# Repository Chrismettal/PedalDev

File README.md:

# PedalDev <!-- omit in toc -->

This is a convenient system for quickly creating stompboxes, as well as a collection of designs made with this system.

The design is split into two boards, a lower and an upper one. The lower PCB handles all of the I/O, switching, and power stuff, while the upper one focuses on the individual effect. The two boards plug together and fit neatly inside a commonly used Hammond 1590B. For each finished design there is also a PCB frontpanel so I don't have to deal with any actual design work and can just hide my designs behind technical looking stuff. The actual boards take full advantage of modern SMD components for optimal space usage.

All designs build up from the same template to allow rapid creation of new designs as well as saving time on recurring steps. There are even various protoboard variants of the upper PCB fitting the same template, to make boutique one-off designs more convenient and robust. For every design you will find the full KiCAD project including schematic and production files like **BOM, Gerbers and PCBA place files** in their respective project folders. (`/pcb/*`)

For easy mechanical manufacturing a 3D printable drilling template is provided. There is also a 3D printable design of the full stompbox similar to the 1590B with all ports "predrilled". A plastic case is not super recommended though and should only be used for quick testing. Conductive spray paint as shielding on the inside is also recommended when using the 3D printed case. (`/3d/*`)

Parts marked with ":construction:" are work in progress and not fully verified yet.

---

Individual boards, predrilled cases as well as kits will be stocked at Tindie!

**If you like my work please consider [supporting my caffeine addiction](https://github.com/Chrismettal#donations)!**

## Table of contents <!-- omit in toc -->

- [Specific Designs](#specific-designs)
  - [404 (:sheep: Ibanez Tubescreamer)](#404-sheep-ibanez-tubescreamer)
  - [YOU WHAT?! (:sheep: emma electronic PisdiYAUwot)](#you-what-sheep-emma-electronic-pisdiyauwot)
  - [:construction: TOP (:sheep: OKKO Dominator)](#construction-top-sheep-okko-dominator)
- [Common PCBs](#common-pcbs)
  - [Lower](#lower)
  - [:construction: Lower Smart](#construction-lower-smart)
- [Protoboards](#protoboards)
  - [Proto Simple](#proto-simple)
- [Designing your own effects](#designing-your-own-effects)
- [Building guide](#building-guide)
  - [Case](#case)
  - [Electronics](#electronics)
- [Sources](#sources)
- [Tools](#tools)
- [Donations](#donations)
- [License](#license)

## Specific Designs

While there aren't many specific designs right now, they will be created faster now that the system is proven working. There is a wide range of devices in the works, from high gain distortions over reverbs to new, experimental stuff.

### 404 (:sheep: Ibanez Tubescreamer)

Based on the popular Tubescreamer this is obviously the first design to be done in this system.

Nothing crazy here, only `D1-3` feature a dual footprint to put in your favourite clipping diodes.

There are two jumpers that need to be set when building this board. `JP1` does not really do anything with the sound but chooses a filter to be sent to ground or to bias voltage as some schematics have it either way. `JP2` however allows choosing betweeen symmetrical or assymetrical clipping.

### YOU WHAT?! (:sheep: emma electronic PisdiYAUwot)

Very cheap in parts but incredibly tight high gain distortion with lots of attack.

### :construction: TOP (:sheep: OKKO Dominator)

:construction: :construction: :construction: **Work in progress** :construction: :construction: :construction:

Based on schematic by Saruman [found here](https://www.freestompboxes.org/viewtopic.php?t=12031&hilit=c6).

First PCB version `f35813b` was broken is currently being debugged. 4 Pins on `TL074` were swapped, `ICL7660` does not work when `BOOST` mode is set (But **`ICL7660S`** does..), and input stage sounds super starved, more like a bassy fuzz than a distortion. Simulation seems to confirm this so confidence in schematic is low. Currently getting hold of an original Dominator for schematic comparison.

Two jumpers on board revision `f35813b` are for debugging the power stage around the `7660` but will probably be removed or clarified on the fixed revision

## Common PCBs

### Lower

The lower PCB consists of the bypass footswitch with a status LED, input and output jacks as well as power input, filtering and FET based reverse polarity protection.

The Input/Output jacks are called `PJ-602B`. These are not available via LCSC sadly, but can be found all over Aliexpress. 

Additionally an optional TL07X based buffer can be enabled via two jumpers. This was only added because the PCB had enough room for it and it can save room on the pedalboard instead of adding a separate buffer box. The buffer parts do NOT NEED to be populated if you intend never to use them. **Either `JP1_A1` and `JP1_B1` or `JP2_A1` and `JP2_B1` need to be set for signal to be passed through**.

The LED is driven through a simple "anti pop" filter and two optional anti-pop bleeders can be enabled via `JP3` and `JP4` to bleed any input/output caps on the connected upper board if neccessary.

Test hooks and pads are sprinkled on interesting signals for effect development and debugging.

> :bulb: Hint: 
> 
> While this system is intended to be used with one lower PCB and one upper PCB fitting together, it might be convenient to just use the lower PCB even if you do not intend to use an actual effect from this system. Doing so greatly reduces the amount of free form wiring and frees up some space on your actual effect PCB.

### :construction: Lower Smart

:construction: :construction: :construction: **Work in progress** :construction: :construction: :construction:

Same as `Lower`, but instead of a true bypass 3PDT Switch it features a microcontroller to turn your effect on and off either in momentary or latching mode. To show the mode it's currently on, it uses a bicolor LED.

On initial bootup, the device will be in latching mode. Pressing the button will toggle the effect on and off. The :construction: colored LED will be on as long as the effect is on in toggle mode. 
Holding the button down for 9 seconds, both LEDs will start blinking, signaling that a mode change is imminent. Holding the button for one more second, the device will switch into momentary mode.
In momentary mode, the effect will only be on while the button is held. While the effect is on, a :construction: colored LED will be on in momentary mode.
Switching back to toggle mode works the same way, by holding down the button long enough.

## Protoboards

### Proto Simple

This is a simple protoboard to use as an "upper" board, allowing for up to 6 pots, or 5 pots with one DPDT print switch.
It features 9V and GND power rails straight through the design to allow for easy power distribution

While it does not allow for the density of SMD components it can certainly fit a lot of designs.

## Designing your own effects

I would love to merge your designs using this system into this repo!

To design your own effect PCB, create a copy of the `UpperRaw` KiCAD project for the actual effect, and `FrontRaw` for a PCB frontpanel design. `UpperRaw` includes a collection of frequently used parts in the schematic, set up with LCSC part numbers etc. It would be great if you add LCSC part numbers to all parts used in your design as well. After merging I will recreate the production files to the same parameters as the already created designs so don't worry about that.

---

## Building guide

As the system tries to use the little space in the 1590B as efficient as possible, the actual build can be quite tight. There is a set order of steps that should be taken to make the build as quick and easy as possible.

The whole system is designed so the PCBs can be ordered from JLCPCB mostly populated, so only very little hand soldering is involved. If you order the boards finished you will mostly have to solder only the through hole components, but for some rare components that JLCPCB doesn't populate, it might be neccessary to solder some SMD components manually. SMD components go down to `0603` for passives, and `SOIC-*` / `SOT-*` for actives, which is still hand solderable without too much trouble. A hot air solder station is highly recommended though.

<details>
  <summary markdown="span">Building guide, click to expand</summary>

### Case

If you have access to a 3D printer (or to my [Tindie Shop](https://www.tindie.com/stores/binary-6/)), there is a printable drill guide available. Otherwise, there will be a techdraw sheet with all the dimensions. At the [shop](https://www.tindie.com/stores/binary-6/) you will also find predrilled, black cases directly manufactured by Hammond.

All models are compatible with the same drill layout. Holes not required for a specific board will be hidden by the front plate, so the fully stacked 6 controls variant works for every model.

1. Put the case in the drill guide and use a center punch to mark out all the holes to be drilled

2. Pre-drill all marked holes with a `3mm drill bit` (The smallest size used on the device)

3. Drill out all the holes to the sizes marked on the drill guide. Note that the holes are all 0.5mm - 1mm larger than they need to be to make alignment of the frontpanel easier

4. If you want to paint the case, this would be the step to do it. I clean the case with rubbing alcohol, prime and paint, while only focusing on the sides of the case as I will hide the top underneath the frontpanels.

### Electronics

1. Some boards require several components to be mounted manually (Check their individual [documentation](#specific-designs)). These will include through hole parts or not easily available active parts for example. In this case, the OpAmp and input stage transistors, as well as connectors need to be placed manually. Note that the pots and switches are NOT placed at this stage!

---

2. The lower PCB also requires some assembly, namely attaching the LED with its spacer and soldering on the board-to-board connector wire. Make sure to set **either `JP1_A1` and `JP1_B1` or `JP2_A1` and `JP2_B1` need to be set for signal to be passed through**.

---

3. On most boards you will also find some configuration jumpers to be set. These include for example the `Buffered - Unbuffered` jumpers for the [Lower](#lower) PCB. Note the individual boards [documentation](#specific-designs).

---

4. Attach the 10mm spacers to upper board, facing the "Towards foot" side. No washers required.

---

5. Prepare the power jack by attaching two solid wires to the jack as shown. Make sure to keep them straight for easier insertion later

---

6. Mount all jacks, pots and switches to the case, optionally applying the FrontPanel. Do the input/output jacks first, as you will need to have some space to tilt the jacks while inserting them both into the case. They will go in VERY tight, but they will fit. For the power jack, make sure that the pins face upwards. Make sure to keep a single nut on the footswitch to have the correct spacing.

---

7. Insert the pots, making sure to put each pot the correct hole for your design. Check out the silkscreen on your upper PCB for that. The nut probably won't have much flesh to grip onto so only handtighten them, or leave them out if necessary. The board will be held by screws later so it's no big deal. I like to straighten the potpins after mounting so I have  an easier time inserting the PCB in the next step. 

---

8. If your board does not use the middle upper pot, place a spacer inside the hole where a screw will go

---

9.  Place the upper board on top of the controls. Might be a bit tricky to align all the holes, but it can be made a bit easier by loosening all the controls screws. While it is also possible to first solder on all the controls, slight misalignments in height will lead to mechanical stress on the board when screwing the controls down later. Soldering it after mounting will ensure a mechanically unstressed board and still allow unmounting the board later by unscrewing the controls.

---

10. Secure the PCB with screws from the front, Screw down all controls tightly and after makind sure your pots all spin freely (not crooked), then solder all controls to the board.

---

11. Place the lower board on top of the I/O

---

12.  Solder down the lower PCB. Note that this board will NOT be easily removeable without unsoldering the controls again!

---

13.  Plug in the board-to-board connector.

---

14.  Screw on the bottom plate and mount your pot knobs.

---

15. Done!

</details>

## Sources

The following 3D models were used for the simulation renders in KiCAD and FreeCAD. Please check their respective licenses if you intend to reuse them.

Any models that are **not** mentioned here were created by me for this project and are subject to the same [license](#license) as the whole repo.

| File                | Link                                                    |
| ------------------- | ------------------------------------------------------- |
| Hammond 1590B       | https://www.hammfg.com/part/1590B                       |
| PJ-602B Audio jacks | https://github.com/afedorov3/3DModels                   |
| Footswitch_3PDT     | https://grabcad.com/library/3pdt-switch-1               |
| 9mm potentiometers  | https://grabcad.com/library/alpha-rd901f-40-15r1-1      |
| DC barrel jack      | https://grabcad.com/library/5-5mm-panel-mount-dc-jack-1 |
| LED 5mm             | https://grabcad.com/library/led-5mm-1#!                 |

## Tools

- PCBs: [KiCAD 6](https://www.kicad.org/)
- 3D CAD: [FreeCAD 0.20](https://www.freecadweb.org/)
- Source code: [PlatformIO](https://platformio.org/)

## Donations

**If you like my work please consider [supporting my caffeine addiction](https://github.com/Chrismettal#donations)!**

## License

 <br />This work is licensed under a <a rel="license" href="http://creativecommons.org/licenses/by-sa/4.0/">Creative Commons Attribution-ShareAlike 4.0 International License</a>.

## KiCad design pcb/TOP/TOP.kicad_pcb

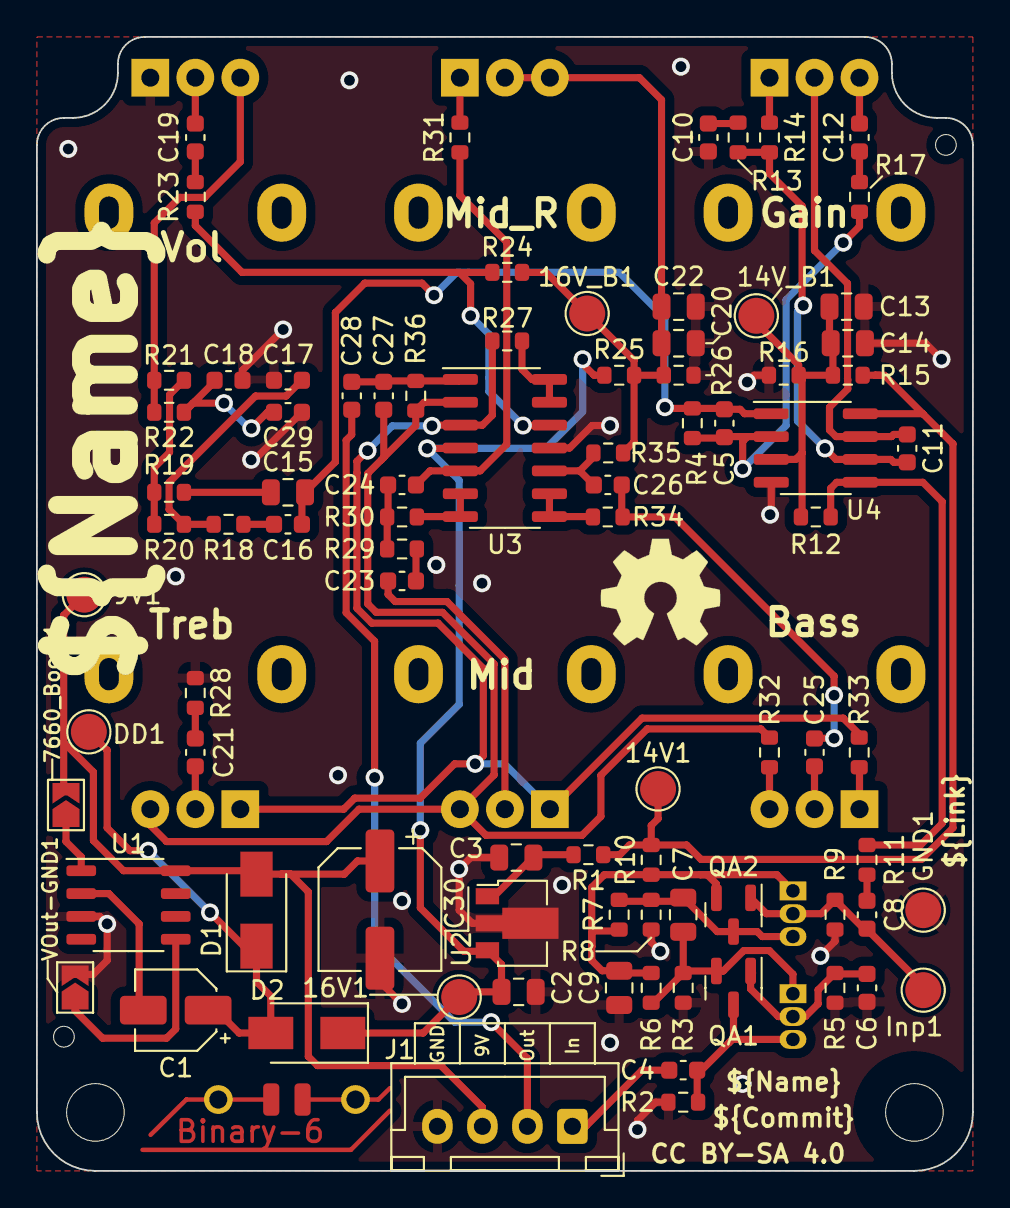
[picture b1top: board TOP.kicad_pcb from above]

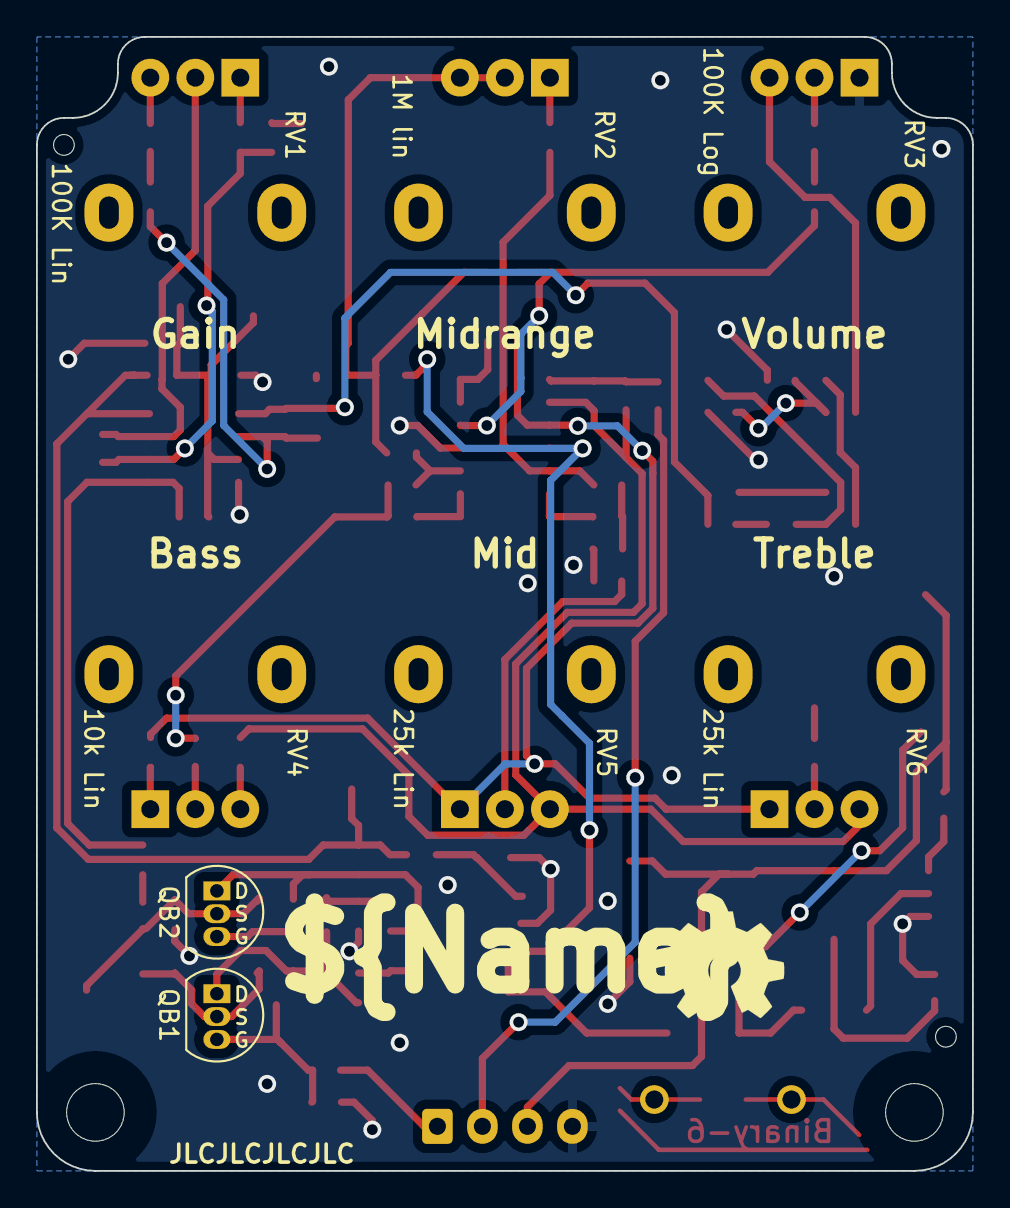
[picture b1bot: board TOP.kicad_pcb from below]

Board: 2 copper layers, 52.0 x 63.0 mm, 96 parts (8 on the bottom side), 56 nets.

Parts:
9V1, 14V1, 14V_B1, 16V1, 16V_B1: TP; TestPoint_Pad_D2.0mm
7660_Boost1: Jmp; SolderJumper-2_P1.3mm_Open_TrianglePad1.0x1.5mm
C1: 10uF; CP_Elec_4x5.4
C2, C3, C9, C13, C14, C20, C22: 10uF; C_0805_2012Metric
C4, C21, C23, C24: 22nF; C_0603_1608Metric
C5: 470pF; C_0603_1608Metric
C6: 2.2uF; C_0603_1608Metric
C7, C15: 10nF; C_0805_2012Metric
C8, C10, C16, C25: 220nF; C_0603_1608Metric
C11: 100pF; C_0603_1608Metric
C12: 100nF; C_0603_1608Metric
C17: 47nF; C_0603_1608Metric
C18, C27, C29: 1nF; C_0603_1608Metric
C19, C28: 470nF; C_0603_1608Metric
C26: 68nF; C_0603_1608Metric
C30: 100uF; CP_Elec_6.3x5.4_Nichicon
D1, D2: 1N4004; D_SMA
DD1: TP; TestPoint_Pad_D2.0mm
GND1: TP; TestPoint_Pad_D2.0mm
H7: Symbol_Binary6; Binary_6_v0.1_tiny_silk
Inp1: TP; TestPoint_Pad_D2.0mm
J1: Conn_01x04; JST_XH_B4B-XH-A_1x04_P2.50mm_Vertical
MK2, MK2#2: Mounting_Hole_M3; EigenesMountingHole_3.2mm_M3_Small
QA1, QA2: BF545A; SOT-23
QB1, QB2: BF245A; TO-92L_Inline
R1: 51R; R_0603_1608Metric
R2, R4, R24: 1M; R_0603_1608Metric
R3, R5, R6, R9, R15, R16, R18, R25, R26, R27, R31, R33, R36: 10K; R_0603_1608Metric
R7, R8, R35: 470K; R_0603_1608Metric
R10, R28: 2K2; R_0603_1608Metric
R11: 22K; R_0603_1608Metric
R12: 100K; R_0603_1608Metric
R13, R23, R32: 1K; R_0603_1608Metric
R14, R29: 7K5; R_0603_1608Metric
R17: 15K; R_0603_1608Metric
R19, R20, R21: 47K; R_0603_1608Metric
R22: 39K; R_0603_1608Metric
R30: 470R; R_0603_1608Metric
R34: 330R; R_0603_1608Metric
RV1: 100K Lin; Potentiometer_Alpha_RD901F-40-00D_Single_Vertical
RV2: 1M lin; Potentiometer_Alpha_RD901F-40-00D_Single_Vertical
RV3: 100K Log; Potentiometer_Alpha_RD901F-40-00D_Single_Vertical
RV4: 10k Lin; Potentiometer_Alpha_RD901F-40-00D_Single_Vertical
RV5, RV6: 25k Lin; Potentiometer_Alpha_RD901F-40-00D_Single_Vertical
U1: ICL7660; SOP-8_3.9x4.9mm_P1.27mm
U2: L78L15_SOT89; SOT-89-3
U3: TL074; SOIC-14_3.9x8.7mm_P1.27mm
U4: OPA2604; SOIC-8_3.9x4.9mm_P1.27mm
VOut-GND1: Jmp; SolderJumper-2_P1.3mm_Open_TrianglePad1.0x1.5mm

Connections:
+9V: 9V1.1, 7660_Boost1.2 (B), C30.1, D1.2 (A), J1.3, U1.8 (V+)
+14V: 14V1.1, R1.1, R10.2, R15.1, U4.8 (V+)
+16V: 16V1.1, C2.1, D2.1 (K), R25.1, U2.3 (IN), U3.4 (V+)
GND: C2.2, C3.2, C6.2, C9.2, C10.1, C13.2, C14.2, C17.1, C18.2, C20.2, C22.2, C29.2, C30.2, GND1.1, J1.4, R2.2, R3.1, R5.2, R8.2, R9.2, R16.2, R26.2, R28.1, RV3.1, U1.3 (GND), U2.2 (GND), U3.11 (V-), U4.4 (V-), VOut-GND1.2 (B)
unnamed: 14V_B1.1, C13.1, C14.1, R12.1, R15.2, R16.1, U4.3 (+)
unnamed: 16V_B1.1, C20.1, C22.1, R24.1, R25.2, R26.1, R35.2, RV2.2, RV2.3
unnamed: C1.1, D1.1 (K), D2.2 (A), DD1.1
unnamed: C1.2, U1.2 (CAP+)
unnamed: C3.1, R1.2, U2.1 (OUT)
unnamed: C4.1, QA1.3 (G), QB1.3 (G), R2.1
unnamed: C5.2, R4.1, R17.2, U4.2 (-)
unnamed: C6.1, QA1.1 (S), QB1.2 (S), R5.1
unnamed: C7.1, QA2.3 (G), QB2.3 (G), R7.2, R8.1
unnamed: C7.2, QA1.2 (D), QB1.1 (D), R3.2, R6.1
unnamed: C8.1, R11.1
unnamed: C8.2, Inp1.1, QA2.1 (S), QB2.2 (S), R9.1
unnamed: C9.1, QA2.2 (D), QB2.1 (D), R6.2, R7.1, R10.1
unnamed: C10.2, R13.1
unnamed: C11.1, RV1.2, U4.7
unnamed: C11.2, R13.2, R14.1, U4.6 (-)
unnamed: C12.1, R17.1
unnamed: C12.2, RV1.3
unnamed: C15.1, R19.1
unnamed: C5.1, C15.2, C16.1, R4.2, U4.1
unnamed: C16.2, R18.1
unnamed: C17.2, R18.2, R20.1
unnamed: C18.1, C29.1, R22.2
unnamed: C19.1, R23.1
unnamed: C19.2, RV3.2
unnamed: C21.1, RV6.2
unnamed: C21.2, R28.2
unnamed: C23.1, R29.2
unnamed: C23.2, RV5.2
unnamed: C24.1, R31.2, U3.5 (+)
unnamed: C24.2, R29.1, R30.1
unnamed: C25.1, C26.2, R34.1
unnamed: C25.2, RV4.2
unnamed: C26.1, R35.1, U3.10 (+)
unnamed: C27.1, C28.2, R36.2, U3.1
unnamed: C27.2, R32.1, R36.1, RV5.3, RV6.3, U3.2 (-)
unnamed: R11.2, R12.2, U4.5 (+)
unnamed: R14.2, RV1.1
unnamed: R19.2, R20.2, R21.1
unnamed: R21.2, R22.1, RV3.3
unnamed: R23.2, R24.2, U3.12 (+)
unnamed: R27.1, U3.13 (-), U3.14
unnamed: R27.2, R33.2, RV5.1, RV6.1, U3.3 (+)
unnamed: R30.2, U3.6 (-), U3.7
unnamed: R31.1, RV2.1
unnamed: R32.2, RV4.3
unnamed: R33.1, RV4.1
unnamed: R34.2, U3.8, U3.9 (-)
unnamed: 7660_Boost1.1 (A), U1.1 (BOOST)
unnamed: U1.5 (VOUT), VOut-GND1.1 (A)
Upper_PCB_Input: C4.2, J1.1
Upper_PCB_Output: C28.1, J1.2

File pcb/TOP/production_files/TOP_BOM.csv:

DEPRECATED
Comment,Designator,Footprint,LCSC
"10uF","C1","Capacitor_SMD:CP_Elec_4x5.4","C445047"
"100pF","C11","Capacitor_SMD:C_0603_1608Metric","C14858"
"100nF","C12","Capacitor_SMD:C_0603_1608Metric","C14663"
"47nF","C17","Capacitor_SMD:C_0603_1608Metric","C1622"
"1nF","C18,C27,C29","Capacitor_SMD:C_0603_1608Metric","C1588"
"470nF","C19,C28","Capacitor_SMD:C_0603_1608Metric","C1623"
"10uF","C2,C3,C9,C13,C14,C20,C22","Capacitor_SMD:C_0805_2012Metric","C15850"
"68nF","C26","Capacitor_SMD:C_0603_1608Metric","C31658"
"100uF","C30","Capacitor_SMD:CP_Elec_6.3x5.4_Nichicon","C111600"
"22nF","C4,C21,C23,C24","Capacitor_SMD:C_0603_1608Metric","C21122"
"470pF","C5","Capacitor_SMD:C_0603_1608Metric","C1620"
"2.2uF","C6","Capacitor_SMD:C_0603_1608Metric","C23630"
"10nF","C7,C15","Capacitor_SMD:C_0805_2012Metric","C1710"
"220nF","C8,C10,C16,C25","Capacitor_SMD:C_0603_1608Metric","C21120"
"1N4004","D1,D2","Diode_SMD:D_SMA","C433394"
"Conn_01x04","J1","Connector_JST:JST_XH_B4B-XH-A_1x04_P2.50mm_Vertical","C144395"
"BF545A","Q1,Q2","Package_TO_SOT_SMD:SOT-23",""
"51R","R1","Resistor_SMD:R_0603_1608Metric","C23197"
"2K2","R10,R28","Resistor_SMD:R_0603_1608Metric","C4190"
"22K","R11","Resistor_SMD:R_0603_1608Metric","C31850"
"100K","R12","Resistor_SMD:R_0603_1608Metric","C25803"
"1K","R13,R23,R32","Resistor_SMD:R_0603_1608Metric","C21190"
"7K5","R14,R29","Resistor_SMD:R_0603_1608Metric","C23234"
"15K","R17","Resistor_SMD:R_0603_1608Metric","C22809"
"47K","R19,R20,R21","Resistor_SMD:R_0603_1608Metric","C25819"
"1M","R2,R4,R24","Resistor_SMD:R_0603_1608Metric","C22935"
"39K","R22","Resistor_SMD:R_0603_1608Metric","C23153"
"10K","R3,R5,R6,R9,R15,R16,R18,R25,R26,R27,R31,R33,R36","Resistor_SMD:R_0603_1608Metric","C25804"
"470R","R30","Resistor_SMD:R_0603_1608Metric","C23179"
"330R","R34","Resistor_SMD:R_0603_1608Metric","C23138"
"470K","R7,R8,R35","Resistor_SMD:R_0603_1608Metric","C23178"
"100K Lin","RV1","MeineBib:Potentiometer_Alpha_RD901F-40-00D_Single_Vertical",""
"1M lin","RV2","MeineBib:Potentiometer_Alpha_RD901F-40-00D_Single_Vertical",""
"100K Log","RV3","MeineBib:Potentiometer_Alpha_RD901F-40-00D_Single_Vertical",""
"10k Lin","RV4","MeineBib:Potentiometer_Alpha_RD901F-40-00D_Single_Vertical",""
"25k Lin","RV5,RV6","MeineBib:Potentiometer_Alpha_RD901F-40-00D_Single_Vertical",""
"ICL7660","U1","Package_SO:SOP-8_3.9x4.9mm_P1.27mm","C356724"
"L78L15_SOT89","U2","Package_TO_SOT_SMD:SOT-89-3","C411742"
"TL074","U3","Package_SO:SOIC-14_3.9x8.7mm_P1.27mm","C6963"
"OPA2604","U4","Package_SO:SOIC-8_3.9x4.9mm_P1.27mm","C30608"

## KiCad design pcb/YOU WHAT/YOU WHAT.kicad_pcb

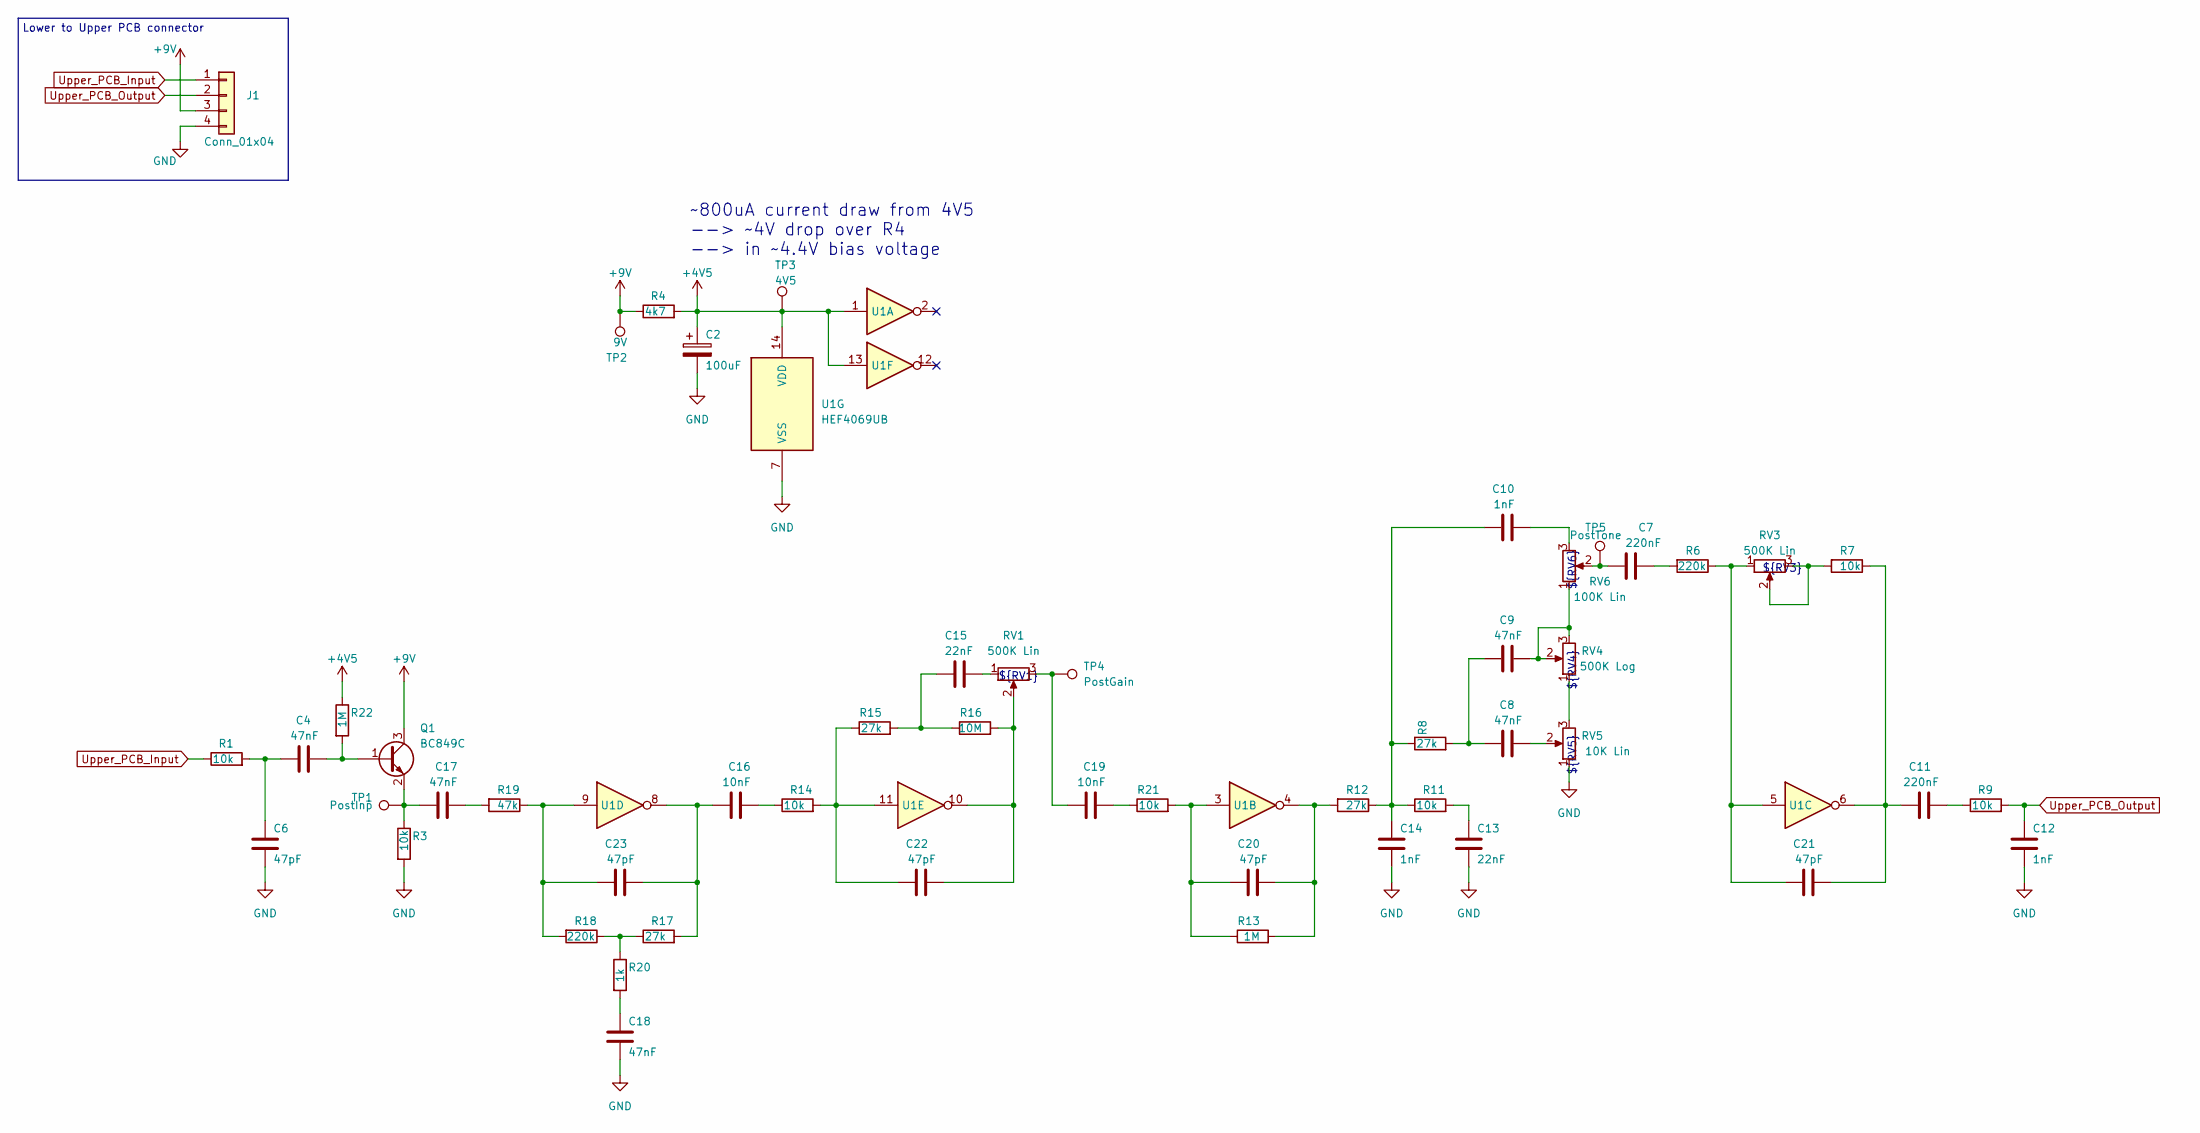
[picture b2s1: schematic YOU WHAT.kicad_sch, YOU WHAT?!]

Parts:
C2: 100uF; CP_Elec_6.3x5.3; LCSC C134723
C4, C8, C9, C17, C18: 47nF; C_0603_1608Metric; LCSC C1622
C6, C20, C21, C22, C23: 47pF; C_0603_1608Metric; LCSC C1671
C7, C11: 220nF; C_0603_1608Metric; LCSC C21120
C10, C12, C14: 1nF; C_0603_1608Metric; LCSC C1588
C13, C15: 22nF; C_0603_1608Metric; LCSC C21122
C16, C19: 10nF; C_0603_1608Metric; LCSC C57112
J1: Conn_01x04; JST_XH_B4B-XH-A_1x04_P2.50mm_Vertical; LCSC C144395
Q1: BC849C; SOT-23; LCSC C334244
R1, R3, R7, R9, R11, R14, R21: 10k; R_0603_1608Metric; LCSC C25804
R4: 4k7; R_0603_1608Metric; LCSC C23162
R6, R18: 220k; R_0603_1608Metric; LCSC C22961
R8, R12, R15, R17: 27k; R_0603_1608Metric; LCSC C22967
R13, R22: 1M; R_0603_1608Metric; LCSC C22935
R16: 10M; R_0603_1608Metric; LCSC C7250
R19: 47k; R_0603_1608Metric; LCSC C25819
R20: 1k; R_0603_1608Metric; LCSC C21190
RV1, RV3: 500K Lin; Potentiometer_Alpha_RD901F-40-00D_Single_Vertical
RV4: 500K Log; Potentiometer_Alpha_RD901F-40-00D_Single_Vertical
RV5: 10K Lin; Potentiometer_Alpha_RD901F-40-00D_Single_Vertical
RV6: 100K Lin; Potentiometer_Alpha_RD901F-40-00D_Single_Vertical
TP1: PostInp; TestPoint_Pad_D2.0mm
TP2: 9V; TestPoint_Pad_D2.0mm
TP3: 4V5; TestPoint_Pad_D2.0mm
TP4: PostGain; TestPoint_Pad_D2.0mm
TP5: PostTone; TestPoint_Pad_D2.0mm
U1: HEF4069UB; SOIC-14_3.9x8.7mm_P1.27mm; LCSC C6739

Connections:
+4V5: C2.1, R4.2, R22.1, TP3.1, U1.1, U1.13, U1.14 (VDD)
+9V: J1.3, Q1.3 (C), R4.1, TP2.1
GND: C2.2, C6.2, C12.2, C13.2, C14.2, C18.2, J1.4, R3.2, RV5.1, U1.7 (VSS)
unnamed: C4.1, C6.1, R1.2
unnamed: C4.2, Q1.1 (B), R22.2
unnamed: C7.1, RV6.2, TP5.1
unnamed: C7.2, R6.2
unnamed: C8.1, C9.1, R8.2
unnamed: C8.2, RV5.2
unnamed: C9.2, RV4.2, RV4.3, RV6.1
unnamed: C10.1, C14.1, R8.1, R11.1, R12.1
unnamed: C10.2, RV6.3
unnamed: C11.1, C21.2, R7.1, U1.6
unnamed: C11.2, R9.1
unnamed: C13.1, R11.2
unnamed: C15.1, RV1.1
unnamed: C15.2, R15.2, R16.1
unnamed: C16.1, C23.2, R17.2, U1.8
unnamed: C16.2, R14.1
unnamed: C17.1, Q1.2 (E), R3.1, TP1.1
unnamed: C17.2, R19.2
unnamed: C18.1, R20.2
unnamed: C19.1, RV1.3, TP4.1
unnamed: C19.2, R21.1
unnamed: C20.1, R13.1, R21.2, U1.3
unnamed: C20.2, R12.2, R13.2, U1.4
unnamed: C21.1, R6.1, RV3.1, U1.5
unnamed: C22.1, R14.2, R15.1, U1.11
unnamed: C22.2, R16.2, RV1.2, U1.10
unnamed: C23.1, R18.2, R19.1, U1.9
unnamed: R7.2, RV3.2, RV3.3
unnamed: R17.1, R18.1, R20.1
unnamed: RV4.1, RV5.3
Upper_PCB_Input: J1.1, R1.1
Upper_PCB_Output: C12.1, J1.2, R9.2

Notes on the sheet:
${RV5}
${RV3}
${RV6}
${RV1}
Lower to Upper PCB connector
${RV4}
~800uA current draw from 4V5 --> ~4V drop over R4 --> in ~4.4V bias voltage

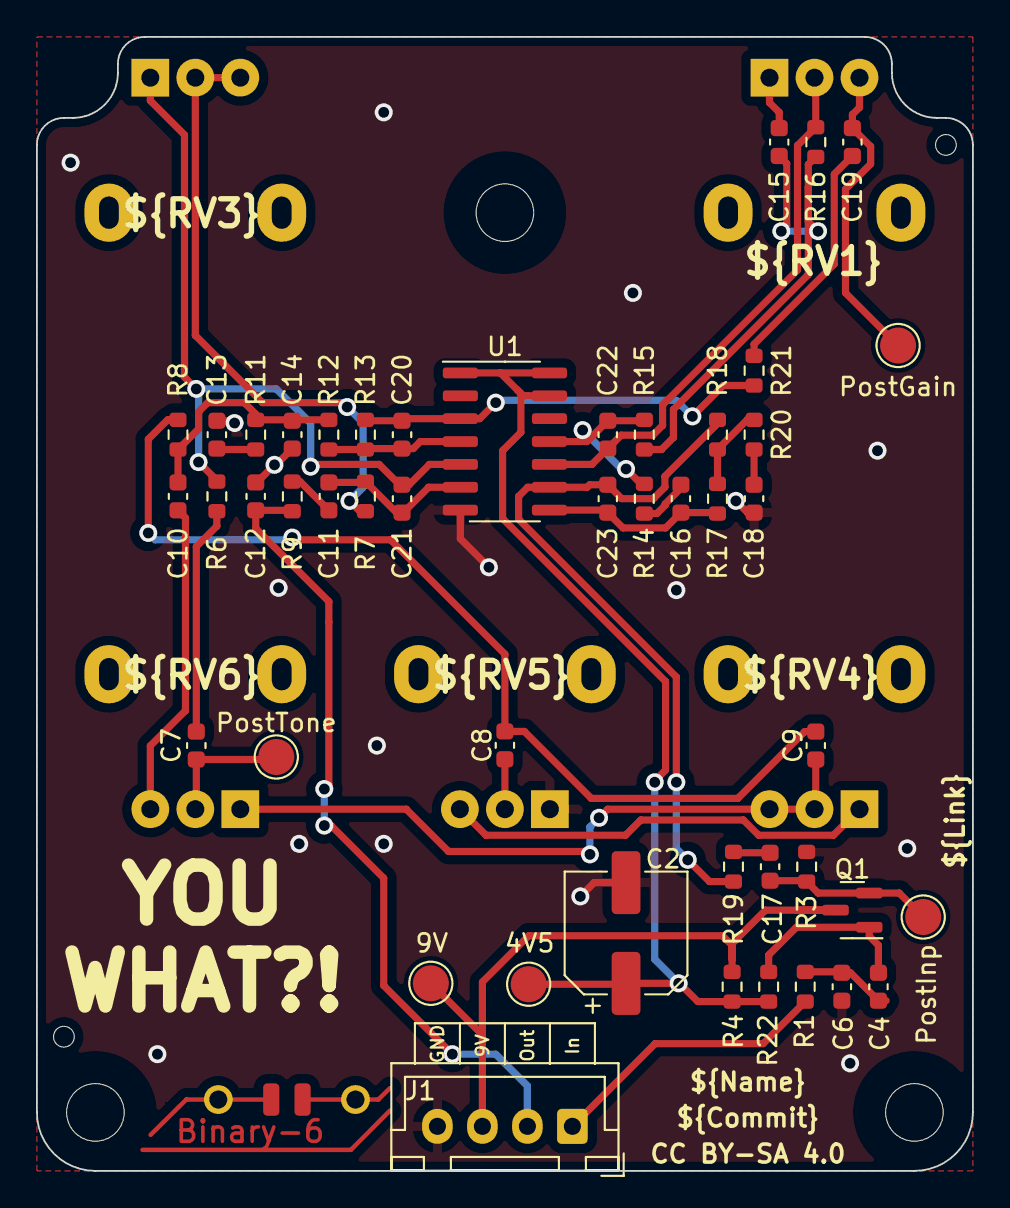
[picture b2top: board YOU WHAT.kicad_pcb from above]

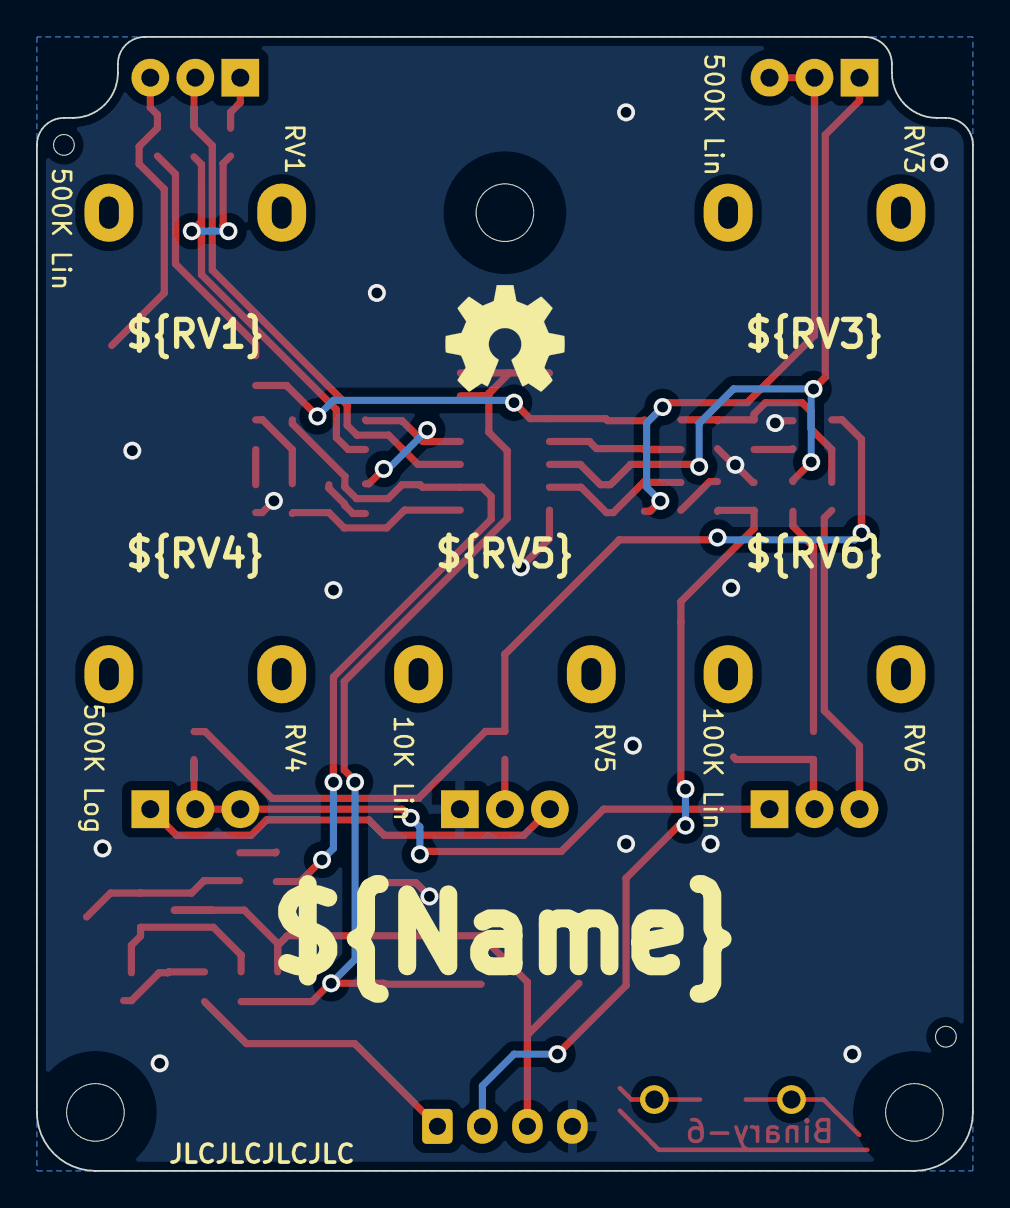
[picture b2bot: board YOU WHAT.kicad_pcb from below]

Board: 2 copper layers, 52.0 x 63.0 mm, 56 parts (5 on the bottom side), 35 nets.

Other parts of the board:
H7: Symbol_Binary6; Binary_6_v0.1_tiny_silk
MK2, MK2#2, MK2#3: Mounting_Hole_M3; EigenesMountingHole_3.2mm_M3_Small

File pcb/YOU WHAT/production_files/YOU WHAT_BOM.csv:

Comment,Designator,Footprint,LCSC
"1nF","C10,C12,C14","Capacitor_SMD:C_0603_1608Metric","C1588"
"22nF","C13,C15","Capacitor_SMD:C_0603_1608Metric","C21122"
"10nF","C16,C19","Capacitor_SMD:C_0603_1608Metric","C57112"
"100uF","C2","Capacitor_SMD:CP_Elec_6.3x5.3","C134723"
"47nF","C4,C8,C9,C17,C18","Capacitor_SMD:C_0603_1608Metric","C1622"
"47pF","C6,C20,C21,C22,C23","Capacitor_SMD:C_0603_1608Metric","C1671"
"220nF","C7,C11","Capacitor_SMD:C_0603_1608Metric","C21120 "
"Conn_01x04","J1","Connector_JST:JST_XH_B4B-XH-A_1x04_P2.50mm_Vertical","C144395"
"BC849C","Q1","Package_TO_SOT_SMD:SOT-23","C334244"
"10k","R1,R3,R7,R9,R11,R14,R21","Resistor_SMD:R_0603_1608Metric","C25804"
"1M","R13,R22","Resistor_SMD:R_0603_1608Metric","C22935"
"10M","R16","Resistor_SMD:R_0603_1608Metric","C7250"
"47k","R19","Resistor_SMD:R_0603_1608Metric","C25819"
"1k","R20","Resistor_SMD:R_0603_1608Metric","C21190"
"4k7","R4","Resistor_SMD:R_0603_1608Metric","C23162"
"220k","R6,R18","Resistor_SMD:R_0603_1608Metric","C22961"
"27k","R8,R12,R15,R17","Resistor_SMD:R_0603_1608Metric","C22967"
"500K Lin","RV1,RV3","MeineBib:Potentiometer_Alpha_RD901F-40-00D_Single_Vertical",""
"500K Log","RV4","MeineBib:Potentiometer_Alpha_RD901F-40-00D_Single_Vertical",""
"10K Lin","RV5","MeineBib:Potentiometer_Alpha_RD901F-40-00D_Single_Vertical",""
"100K Lin","RV6","MeineBib:Potentiometer_Alpha_RD901F-40-00D_Single_Vertical",""
"HEF4069UB","U1","Package_SO:SOIC-14_3.9x8.7mm_P1.27mm","C6739"

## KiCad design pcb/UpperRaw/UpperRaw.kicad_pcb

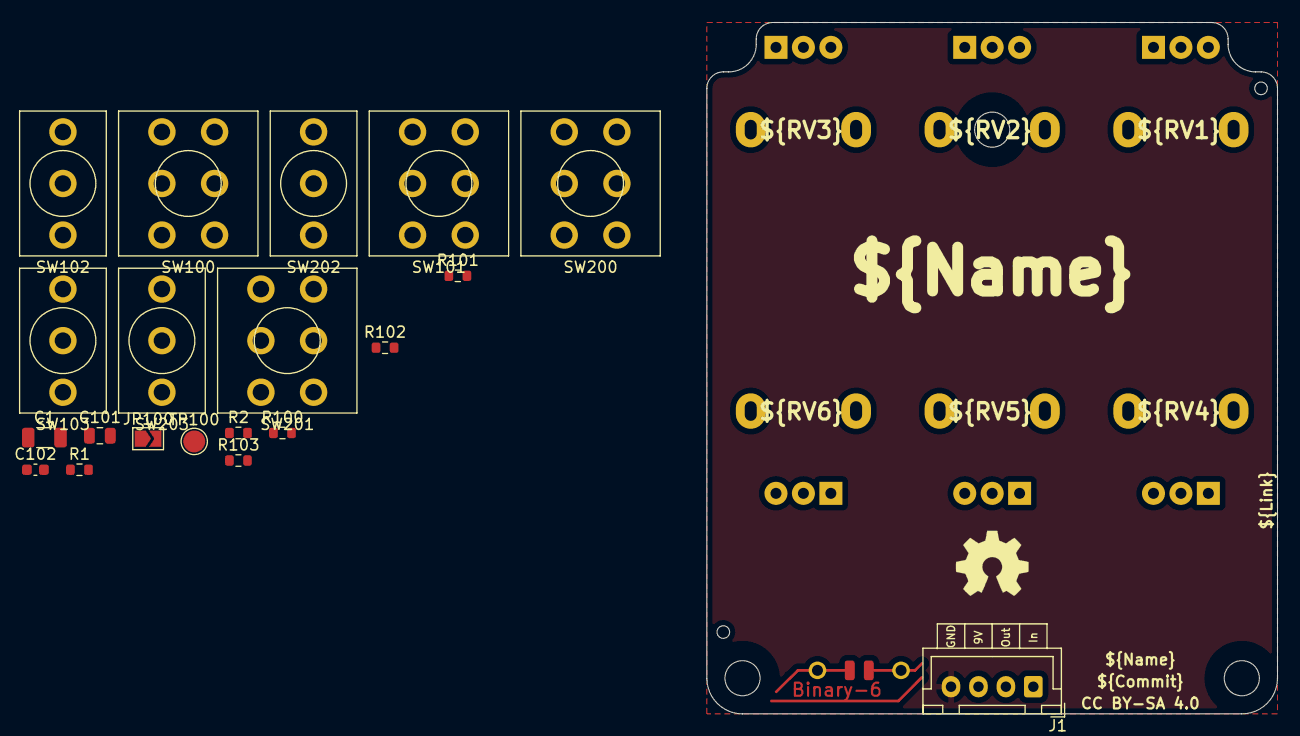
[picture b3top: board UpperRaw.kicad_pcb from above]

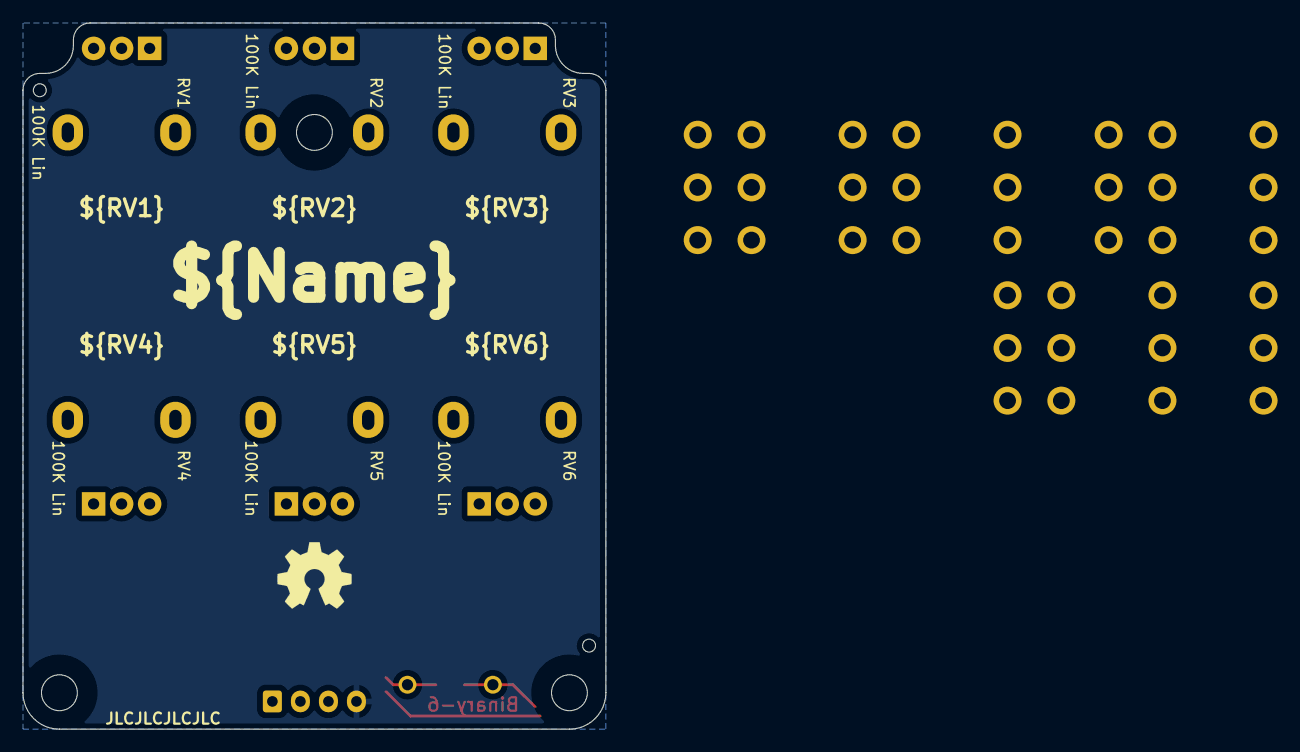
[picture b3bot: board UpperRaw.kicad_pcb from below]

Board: 2 copper layers, 52.0 x 63.0 mm, 30 parts (6 on the bottom side), 3 nets, no tracks yet.

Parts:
C1: 22uF; C_1206_3216Metric
C101: 10uF; C_0805_2012Metric
C102: 220nF; C_0603_1608Metric
H7: Symbol_Binary6; Binary_6_v0.1_tiny_silk
J1: Conn_01x04; JST_XH_B4B-XH-A_1x04_P2.50mm_Vertical
JP100: Jmp; SolderJumper-2_P1.3mm_Open_TrianglePad1.0x1.5mm
MK2, MK2#2, MK2#3: Mounting_Hole_M3; EigenesMountingHole_3.2mm_M3_Small
R1, R2: 10K; R_0603_1608Metric
R100: 1M; R_0603_1608Metric
R101: 2M2; R_0603_1608Metric
R102: 390R; R_0603_1608Metric
R103: 2k2; R_0603_1608Metric
RV1, RV2, RV3, RV4, RV5, RV6: 100K Lin; Potentiometer_Alpha_RD901F-40-00D_Single_Vertical
SW100, SW101, SW200, SW201: SW_DPDT_x2; Switch_toggle_DPDT_Print
SW102, SW103, SW202, SW203: SW_SPDT; Switch_toggle_SPDT_Print
TP100: TP; TestPoint_Pad_D2.0mm

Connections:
+4V5: C1.1, R1.2, R2.1
+9V: J1.3, R1.1
GND: C1.2, J1.4, R2.2

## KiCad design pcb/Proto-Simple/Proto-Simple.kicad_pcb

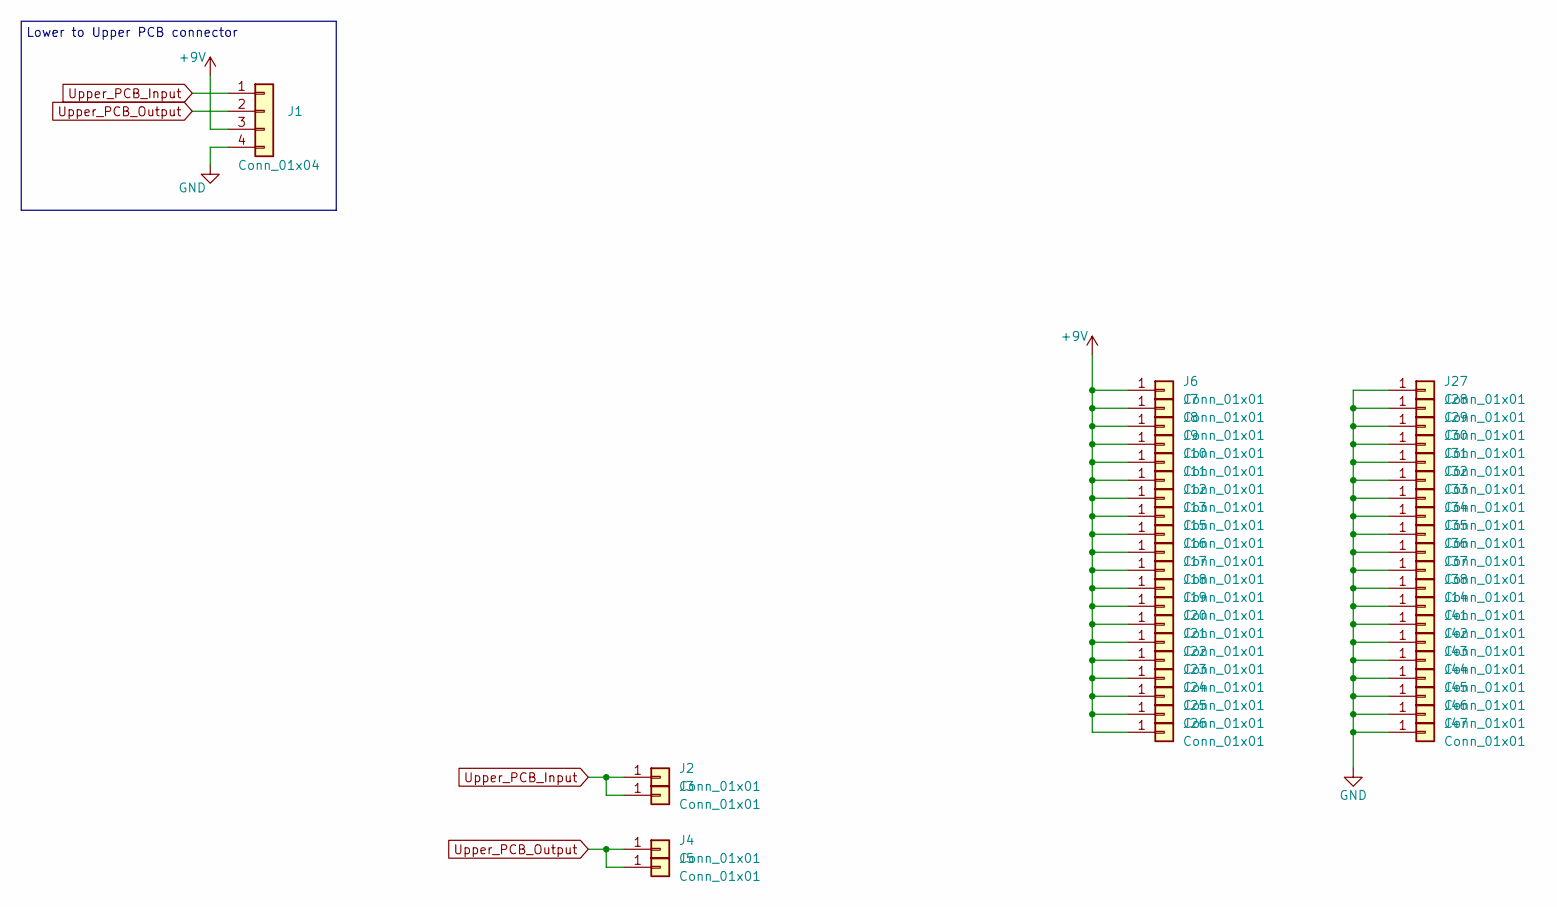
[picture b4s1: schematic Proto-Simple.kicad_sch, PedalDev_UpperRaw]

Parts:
J1: Conn_01x04; JST_XH_B4B-XH-A_1x04_P2.50mm_Vertical; LCSC^ C144395
J2, J3, J4, J5, J6, J7, J8, J9, J10, J11, J12, J13, J14, J15, J16, J17, J18, J19, J20, J21, J22, J23, J24, J25, J26, J27, J28, J29, J30, J31, J32, J33, J34, J35, J36, J37, J38, J41, J42, J43, J44, J45, J46, J47: Conn_01x01; Protopin_Small

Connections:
+9V: J1.3, J6.1, J7.1, J8.1, J9.1, J10.1, J11.1, J12.1, J13.1, J15.1, J16.1, J17.1, J18.1, J19.1, J20.1, J21.1, J22.1, J23.1, J24.1, J25.1, J26.1
GND: J1.4, J14.1, J27.1, J28.1, J29.1, J30.1, J31.1, J32.1, J33.1, J34.1, J35.1, J36.1, J37.1, J38.1, J41.1, J42.1, J43.1, J44.1, J45.1, J46.1, J47.1
Upper_PCB_Input: J1.1, J2.1, J3.1
Upper_PCB_Output: J1.2, J4.1, J5.1

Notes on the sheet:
Lower to Upper PCB connector

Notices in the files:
README.md:
License: CC BY-SA 4.0
pcb/404/404.kicad_pcb:
CC BY-SA 4.0
